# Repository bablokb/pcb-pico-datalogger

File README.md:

Pico Datalogger with Integrated Power-Management
================================================

This repository is no longer maintained, since it was split up
into independent repositories:

Software
--------

  - <https://github.com/bablokb//cp-datalogger>:
    CircuitPython Framework for Power-Optimized, Low-Frequency Datalogging

PCB
---

  - <https://github.com/bablokb//pcb-datalogger-v4e>:
    Stripped down Pico board for data-logging.
    No power-management and no XTSD storage, but Ethernet ready.
  - <https://github.com/bablokb//pcb-datalogger-v3>:
    Fully equipped, all-in-one Pico board for data-logging with power-management and XTSD storage.
  - <https://github.com/bablokb//pcb-datalogger-v2>:
    Pico board for data-logging with power-management and XTSD storage. Needs the
    sensor PCB.
  - <https://github.com/bablokb//pcb-datalogger-sensor-pcb>:
    Sensor PCB for the Pico Datalogger-v2.
  - <https://github.com/bablokb//pcb-datalogger-display-adapter-v2>:
    Display-Adapter PCB with socket-connector (for datalogger-v3/v4e).
  - <https://github.com/bablokb//pcb-datalogger-display-adapter>:
    Display-Adapter PCB with SUR-connector (for datalogger-v2/v3).
  - <https://github.com/bablokb//pcb-datalogger-lora-adapter>:
    LoRa-Adapter PCB (adds SUR-connector to Adafruit-Breakout, for datalogger-v2).
  - <https://github.com/bablokb//pcb-datalogger-lora-pcb>:
    A PCB with a LoRa tranceiver and a SUR connector (for datalogger-v2).
  - <https://github.com/bablokb//pcb-datalogger-v1>:
    First generation Pico board for data-logging with power-management and SD-card storage.
  - <https://github.com/bablokb//pcb-surs-cable-tester>:
    A small PCB to test the type of a 8-pin SUR cable.

3D-Files
--------

  - <https://github.com/bablokb//3D-datalogger-v3-case>:
    3D Design Files for a Case for the Pico-Datalogger-v3
  - <https://github.com/bablokb//3D-datalogger-v2-case>:
    3D Design Files for a Case for the Pico-Datalogger-v2
  - <https://github.com/bablokb//3D-datalogger-stevenson>:
    3D-design-files (supports, OpenSCAD) for a Stevenson Screen Enclosure
  - <https://github.com/bablokb//3D-datalogger-v1-case>:
    3D Design Files for a Case for the Pico-Datalogger-v1

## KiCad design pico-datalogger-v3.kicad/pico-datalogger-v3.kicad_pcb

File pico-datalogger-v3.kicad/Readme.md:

KiCAD-Designfiles for Version 3 PCB
===================================

Here are the KiCAD (v7) design-files for the Datalogger-V3-PCB.

Schematic
---------

Layout
------

3D-Views
--------

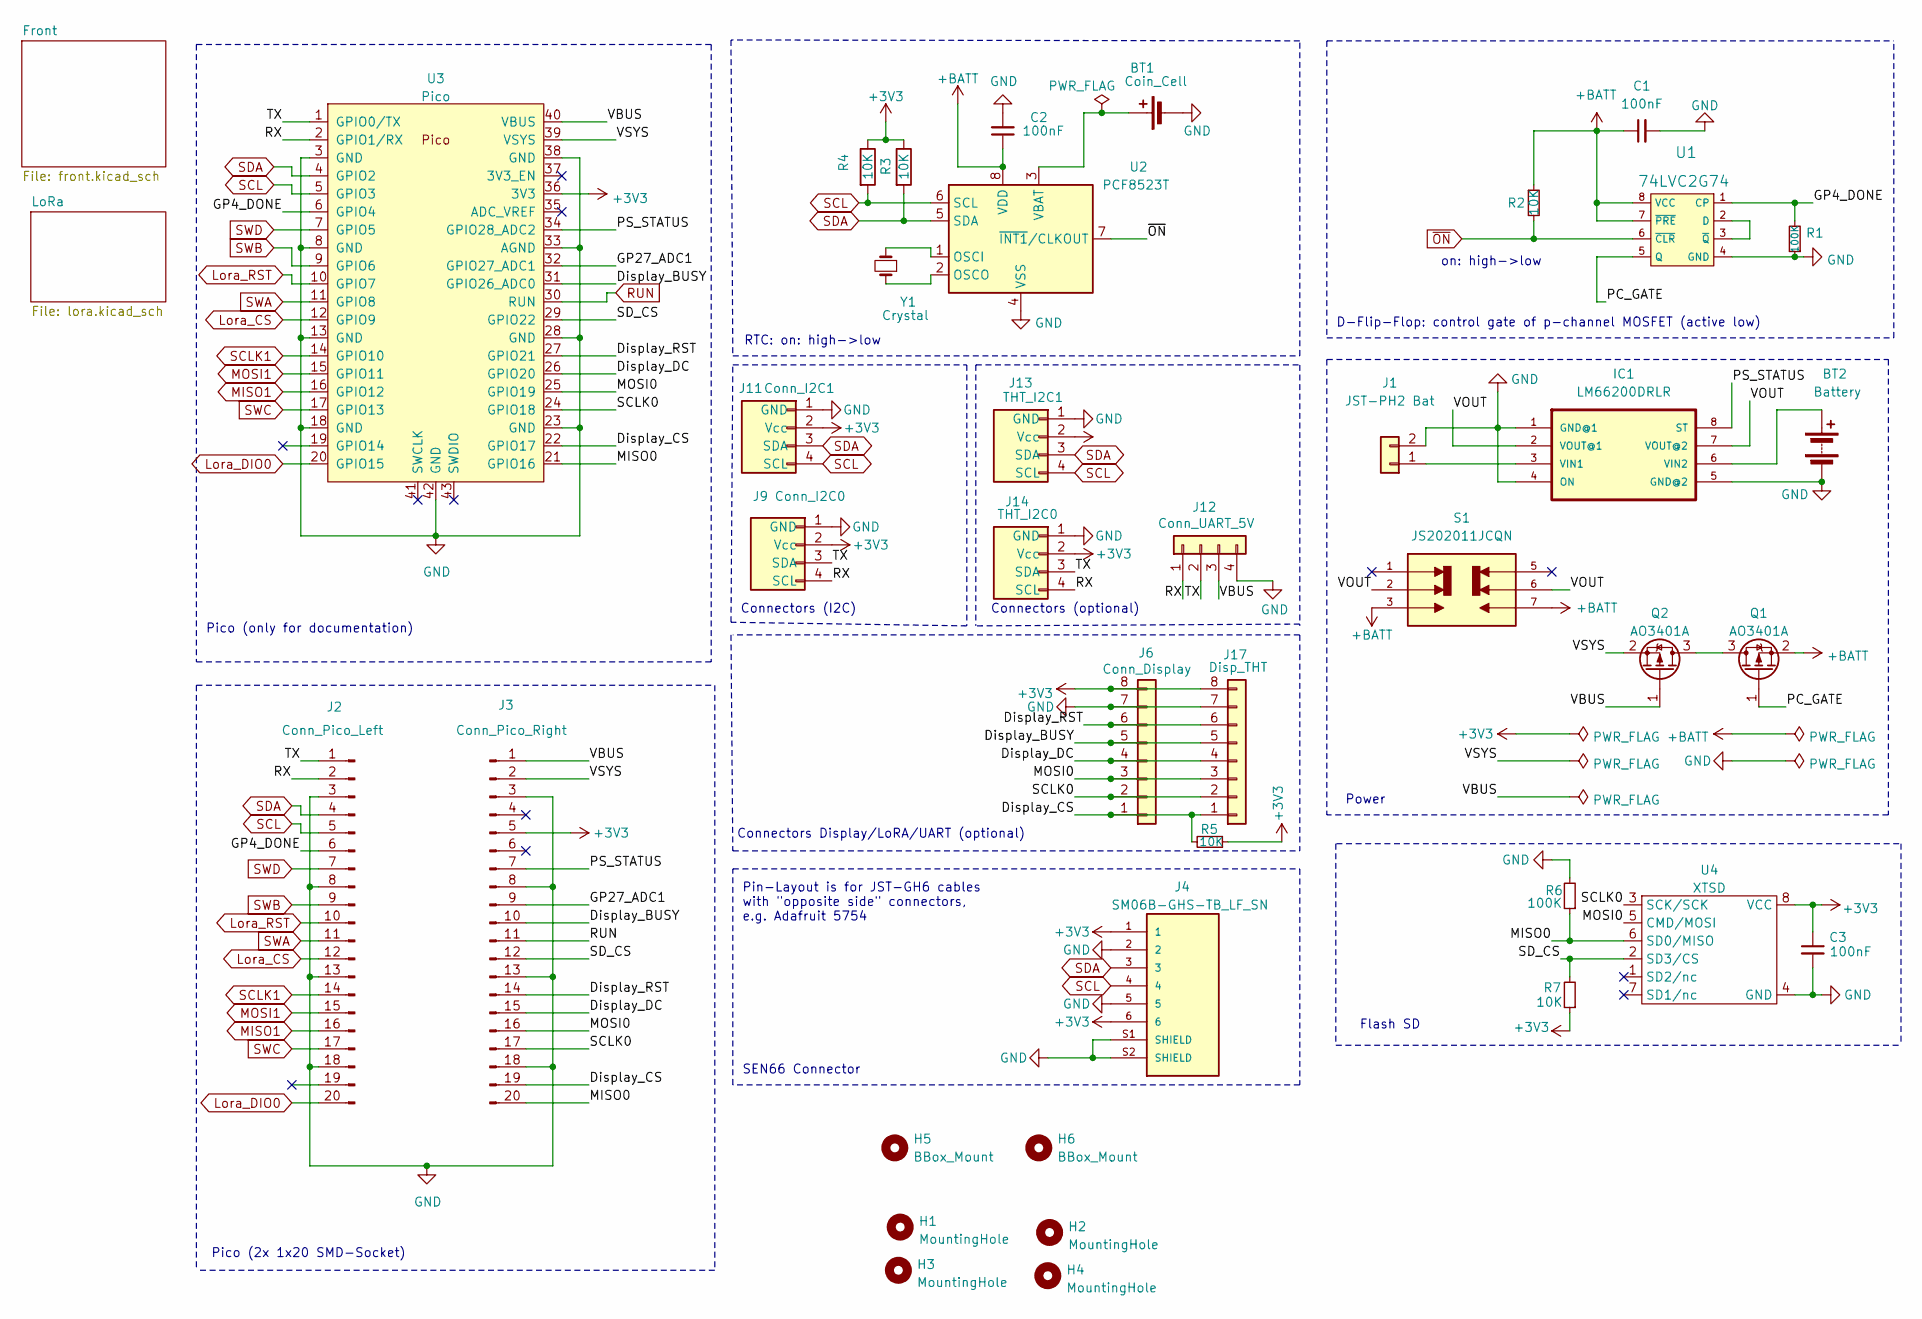
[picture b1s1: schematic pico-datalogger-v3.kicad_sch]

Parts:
BT1: Coin_Cell; CR2032_Holder; LCSC C964777
BT2: Battery; BatteryHolder_Keystone_2462_2xAA; LCSC C3029547
C1, C2, C3: 100nF; C_0402_1005Metric; LCSC C1525
H1, H2, H3, H4: MountingHole; MountingHole_2.5mm
H5, H6: BBox_Mount; MountingHole_3.5_slotted
IC1: LM66200DRLR; LCSC C3235556
J1: JST-PH2 Bat; JST_PH_S2B-PH-SM4-TB_1x02-1MP_P2.00mm_Horizontal; LCSC C295747
J2: Conn_Pico_Left; PinSocket_1x20_P2.54mm_Vertical; LCSC C429947
J3: Conn_Pico_Right; PinSocket_1x20_P2.54mm_Vertical; LCSC C429947
J4: SM06B-GHS-TB_LF_SN; JST_SM06B-GHS-TB_LF_SN; LCSC C133065
J6: Conn_Display; JST_SUR_BM08B-SURS-TF_1x08-1MP_P0.80mm_Vertical; LCSC C5143489
J9: Conn_I2C0; JST_SH_SM04B-SRSS-TB_1x04-1MP_P1.00mm_Horizontal; LCSC C160404
J11: Conn_I2C1; JST_SH_SM04B-SRSS-TB_1x04-1MP_P1.00mm_Horizontal; LCSC C160404
J12: Conn_UART_5V; PinHeader_1x04_P2.54mm_Horizontal
J13: THT_I2C1; PinHeader_1x04_P2.54mm_Vertical
J14: THT_I2C0; PinHeader_1x04_P2.54mm_Vertical
J17: Disp_THT; PinHeader_1x08_P2.54mm_Vertical
Q1, Q2: AO3401A; SOT-23; LCSC C15127
R1, R6: 100K; R_0402_1005Metric; LCSC C25741
R2, R3, R4, R5, R7: 10K; R_0402_1005Metric; LCSC C25744
S1: JS202011JCQN; SW_JS202011JCQN; LCSC C221665
U1: 74LVC2G74; TSSOP-8_3x3mm_P0.65mm; MPN SN74HC74N; Digi-Key_PN 296-1602-5-ND
U2: PCF8523T; SOIC-8_3.9x4.9mm_P1.27mm; LCSC C2651516
U3: Pico; RPi_Pico_TH_nodbg
U4: XTSD; LCSC C7429710
Y1: Crystal; Crystal_SMD_3215-2Pin_3.2x1.5mm; LCSC C32346

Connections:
+3V3: C3.1, J3.5, J4.1, J4.6, J6.8, J9.2 (Vcc), J11.2 (Vcc), J13.2 (Vcc), J14.2 (Vcc), J17.8, R3.1, R4.1, R5.1, R7.1, U3.36 (3V3), U4.8 (VCC); also elsewhere on the board
+BATT: C1.1, C2.1, Q1.2 (S), R2.1, S1.3, S1.7, U1.7 (~PRE), U1.8 (VCC), U2.8 (VDD)
/Display_BUSY: J3.10, J6.5, J17.5, U3.31 (GPIO26_ADC0)
/Display_CS: J3.19, J6.1, J17.1, R5.2, U3.22 (GPIO17)
/Display_DC: J3.15, J6.4, J17.4, U3.26 (GPIO20)
/Display_RST: J3.14, J6.6, J17.6, U3.27 (GPIO21)
/GP4_DONE: J2.6, R1.2, U1.1 (CP), U3.6 (GPIO4)
/GP27_ADC1: J3.9, U3.32 (GPIO27_ADC1)
/MISO0: J3.20, R6.1, U3.21 (GPIO16), U4.6 (SD0/MISO)
/MOSI0: J3.16, J6.3, J17.3, U3.25 (GPIO19), U4.5 (CMD/MOSI)
/PC_GATE: Q1.1 (G), U1.5 (Q)
/PS_STATUS: IC1.8 (ST), J3.7, U3.34 (GPIO28_ADC2)
/RX: J2.2, J9.4 (SCL), J12.1, J14.4 (SCL), U3.2 (GPIO1/RX)
/SCLK0: J3.17, J6.2, J17.2, U3.24 (GPIO18), U4.3 (SCK/SCK)
/SD_CS: J3.12, R7.2, U3.29 (GPIO22), U4.2 (SD3/CS)
/TX: J2.1, J9.3 (SDA), J12.2, J14.3 (SDA), U3.1 (GPIO0/TX)
/VBUS: J3.1, J12.3, Q2.1 (G), U3.40 (VBUS)
/VOUT: IC1.2 (VOUT@1), IC1.7 (VOUT@2), S1.2, S1.6
/VSYS: J3.2, Q2.2 (S), U3.39 (VSYS)
GND: BT1.2 (-), BT2.2 (-), C1.2, C2.2, C3.2, IC1.1 (GND@1), IC1.4 (ON), IC1.5 (GND@2), J1.2, J2.3, J2.8, J2.13, J2.18, J3.3, J3.8, J3.13, J3.18, J4.2, J4.5, J4.S1 (SHIELD), J4.S2 (SHIELD), J6.7, J9.1 (GND), J11.1 (GND), J12.4, J13.1 (GND), J14.1 (GND), J17.7, R1.1, R6.2, U1.4 (GND), U2.4 (VSS), U3.3 (GND), U3.8 (GND), U3.13 (GND), U3.18 (GND), U3.23 (GND), U3.28 (GND), U3.33 (AGND), U3.38 (GND), U3.42 (GND), U4.4 (GND); also elsewhere on the board
Lora_CS: J2.12, U3.12 (GPIO9); also elsewhere on the board
Lora_DIO0: J2.20, U3.20 (GPIO15); also elsewhere on the board
Lora_RST: J2.10, U3.10 (GPIO7); also elsewhere on the board
MISO1: J2.16, U3.16 (GPIO12); also elsewhere on the board
MOSI1: J2.15, U3.15 (GPIO11); also elsewhere on the board
unnamed: BT1.1 (+), U2.3 (VBAT)
unnamed: BT2.1 (+), IC1.6 (VIN2)
unnamed: IC1.3 (VIN1), J1.1
unnamed: Q1.3 (D), Q2.3 (D)
unnamed: U1.2 (D), U1.3 (~Q)
unnamed: U2.1 (OSCI), Y1.2
unnamed: U2.2 (OSCO), Y1.1
RUN: J3.11; also elsewhere on the board
SCL: J2.5, J4.4, J11.4 (SCL), J13.4 (SCL), R4.2, U2.6 (SCL), U3.5 (GPIO3); also elsewhere on the board
SCLK1: J2.14, U3.14 (GPIO10); also elsewhere on the board
SDA: J2.4, J4.3, J11.3 (SDA), J13.3 (SDA), R3.2, U2.5 (SDA), U3.4 (GPIO2); also elsewhere on the board
SWA: J2.11, U3.11 (GPIO8); also elsewhere on the board
SWB: J2.9, U3.9 (GPIO6); also elsewhere on the board
SWC: J2.17, U3.17 (GPIO13); also elsewhere on the board
SWD: J2.7, U3.7 (GPIO5); also elsewhere on the board
~ON: R2.2, U1.6 (~CLR), U2.7 (~INT1/CLKOUT); also elsewhere on the board

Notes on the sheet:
on: high->low
D-Flip-Flop: control gate of p-channel MOSFET (active low)
Connectors Display/LoRA/UART (optional)
Pico (only for documentation)
Power
Pico (2x 1x20 SMD-Socket)
SEN66 Connector
RTC: on: high->low
Connectors (optional)
Pin-Layout is for JST-GH6 cables with "opposite side" connectors, e.g. Adafruit 5754
Connectors (I2C)
Flash SD

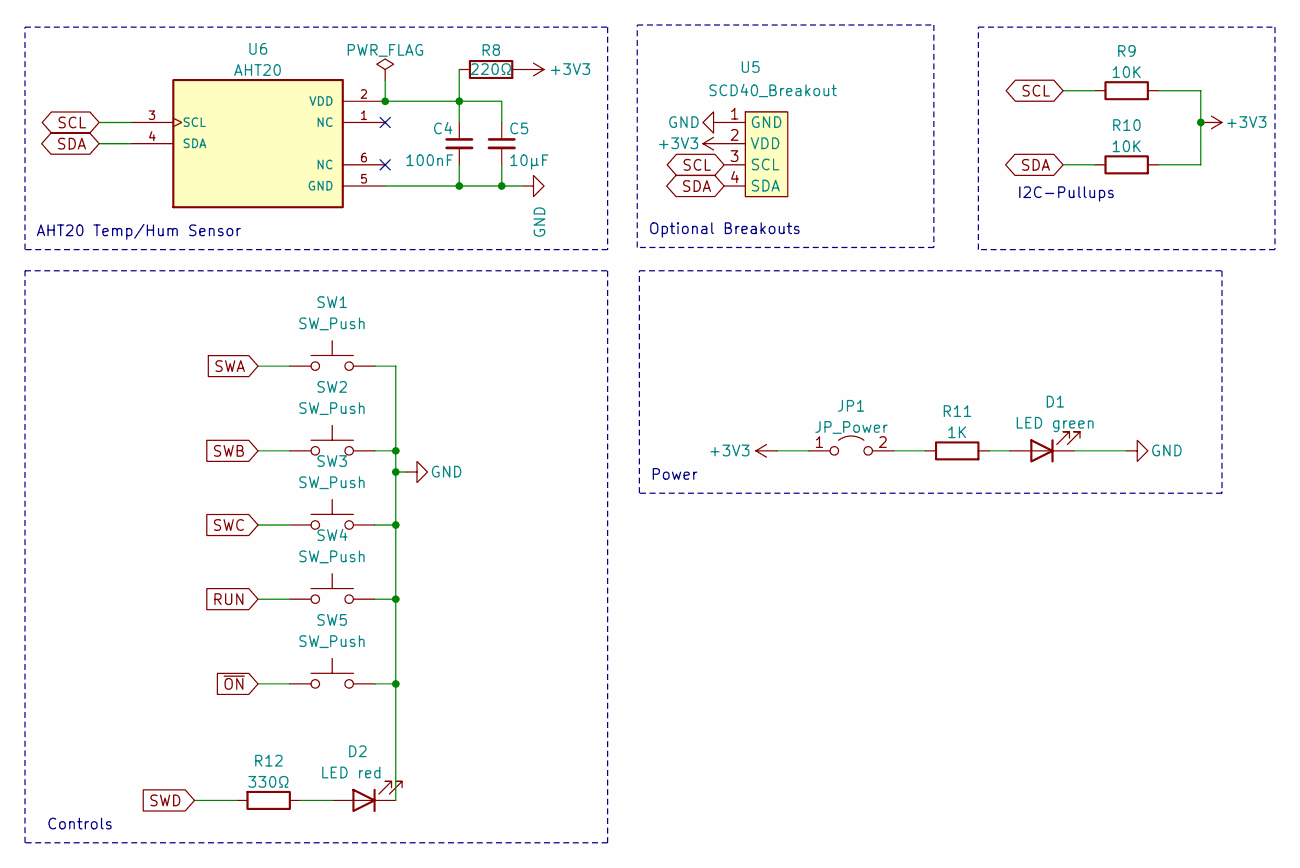
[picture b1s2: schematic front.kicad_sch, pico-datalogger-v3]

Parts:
C4: 100nF; C_0402_1005Metric; LCSC C1525
C5: 10µF; C_0603_1608Metric; LCSC C19702
D1: LED green; LED_0805_2012Metric; LCSC C2297
D2: LED red; LED_0805_2012Metric; LCSC C84256
JP1: JP_Power; SolderJumper-2_P1.3mm_Open_Pad1.0x1.5mm
R8: 220Ω; R_0402_1005Metric; LCSC C25091
R9, R10: 10K; R_0402_1005Metric; LCSC C25744
R11: 1K; R_0402_1005Metric; LCSC C11702
R12: 330Ω; R_0402_1005Metric; LCSC C25104
SW1, SW2, SW3, SW4, SW5: SW_Push; SW_SPST_B3S-1000; LCSC C221869
U5: SCD40_Breakout
U6: AHT20; LCSC C3012622

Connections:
+3V3: JP1.1 (A), R8.2, R9.2, R10.2, U5.2 (VDD); also elsewhere on the board
GND: C4.2, C5.2, D1.1 (K), D2.1 (K), SW1.2, SW2.2, SW3.2, SW4.2, SW5.2, U5.1 (GND), U6.5 (GND); also elsewhere on the board
unnamed: D1.2 (A), R11.2
unnamed: D2.2 (A), R12.1
unnamed: JP1.2 (B), R11.1
unnamed: C4.1, C5.1, R8.1, U6.2 (VDD)
RUN: SW4.1; also elsewhere on the board
SCL: R9.1, U5.3 (SCL), U6.3 (SCL); also elsewhere on the board
SDA: R10.1, U5.4 (SDA), U6.4 (SDA); also elsewhere on the board
SWA: SW1.1; also elsewhere on the board
SWB: SW2.1; also elsewhere on the board
SWC: SW3.1; also elsewhere on the board
SWD: R12.2; also elsewhere on the board
~ON: SW5.1; also elsewhere on the board

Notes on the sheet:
Optional Breakouts
AHT20 Temp/Hum Sensor
Power
I2C-Pullups
Controls

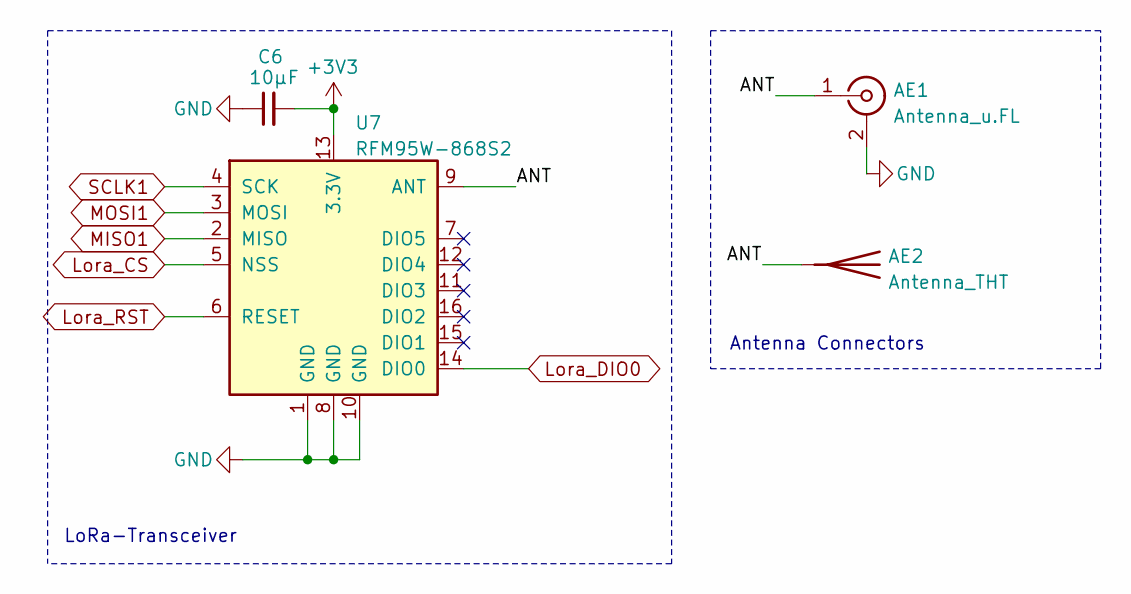
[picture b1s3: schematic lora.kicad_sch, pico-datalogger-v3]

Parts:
AE1: Antenna_u.FL; U.FL_Hirose_U.FL-R-SMT-1_Vertical; LCSC C88374
AE2: Antenna_THT
C6: 10µF; C_0603_1608Metric; LCSC C19702
U7: RFM95W-868S2; HOPERF_RFM9XW_SMD; LCSC C2844472

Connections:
+3V3: C6.2, U7.13 (3.3V); also elsewhere on the board
/LoRa/ANT: AE1.1 (In), AE2.1 (A), U7.9 (ANT)
GND: AE1.2 (Ext), C6.1, U7.1 (GND), U7.8 (GND), U7.10 (GND); also elsewhere on the board
Lora_CS: U7.5 (NSS); also elsewhere on the board
Lora_DIO0: U7.14 (DIO0); also elsewhere on the board
Lora_RST: U7.6 (RESET); also elsewhere on the board
MISO1: U7.2 (MISO); also elsewhere on the board
MOSI1: U7.3 (MOSI); also elsewhere on the board
SCLK1: U7.4 (SCK); also elsewhere on the board

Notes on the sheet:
Antenna Connectors
LoRa-Transceiver

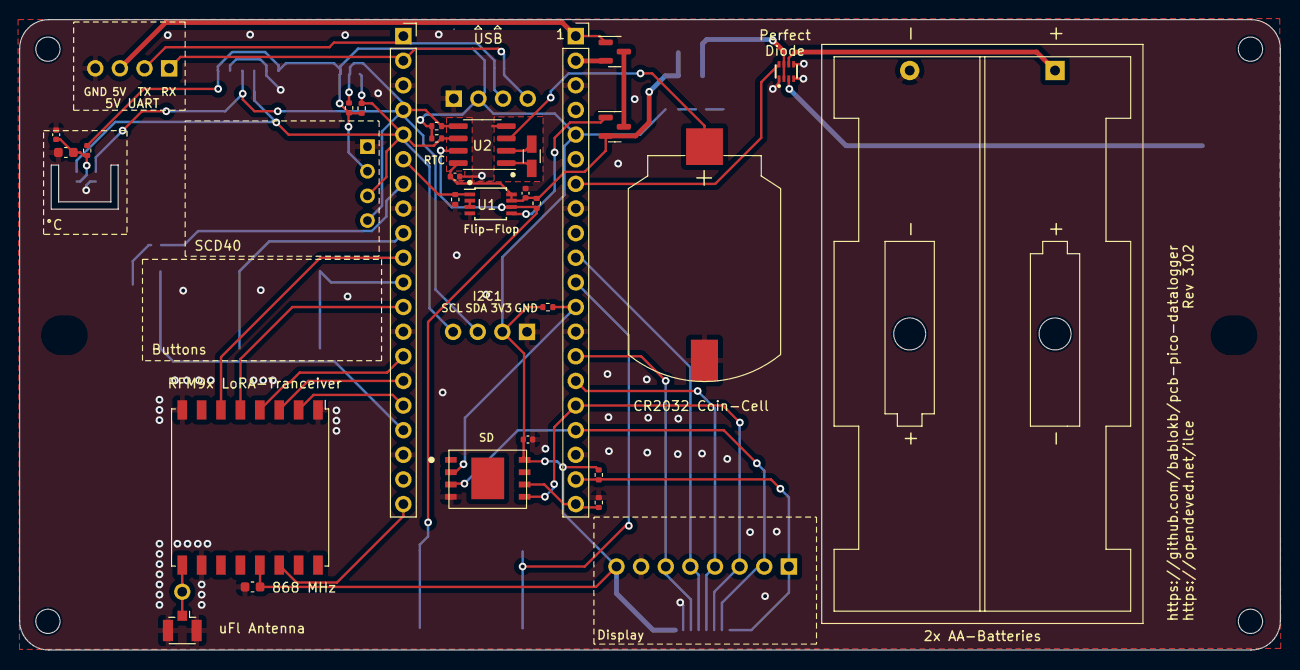
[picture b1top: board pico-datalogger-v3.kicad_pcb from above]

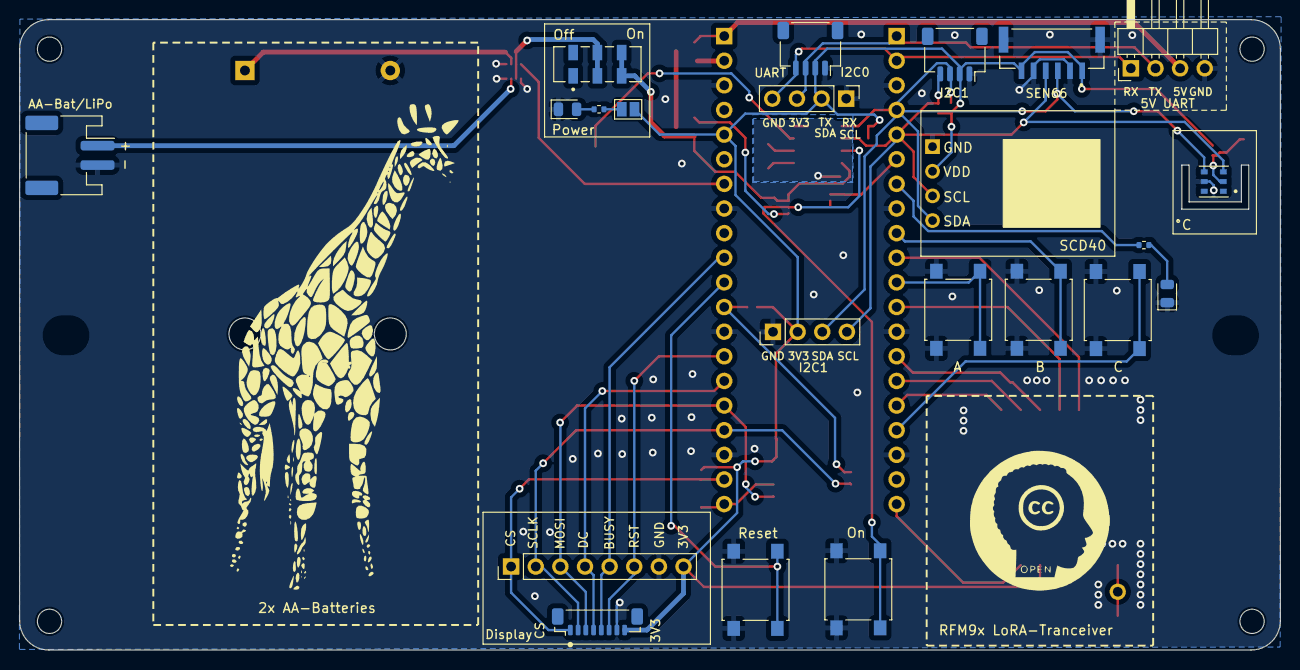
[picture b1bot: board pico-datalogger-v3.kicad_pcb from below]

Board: 2 copper layers, 130.0 x 65.0 mm, 58 parts (22 on the bottom side), 45 nets.

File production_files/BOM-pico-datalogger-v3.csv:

Comment,Designator,Footprint,LCSC
1K,R11,R_0402_1005Metric,C11702
SM06B-GHS-TB_LF_SN,J4,JST_SM06B-GHS-TB_LF_SN,C133065
AO3401A,"Q1,Q2",SOT-23,C15127
100nF,"C1,C2,C3,C4",C_0402_1005Metric,C1525
Conn_I2C1,"J11,J9",JST_SH_SM04B-SRSS-TB_1x04-1MP_P1.00mm_Horizontal,C160404
10µF,"C5,C6",C_0603_1608Metric,C19702
JS202011JCQN,S1,SW_JS202011JCQN,C221665
SW_Push,"SW1,SW2,SW3,SW4,SW5",SW_SPST_B3S-1000,C221869
LED green,D1,LED_0805_2012Metric,C2297
220Ω,R8,R_0402_1005Metric,C25091
330Ω,R12,R_0402_1005Metric,C25104
100K,"R1,R6",R_0402_1005Metric,C25741
10K,"R10,R2,R3,R4,R5,R7,R9",R_0402_1005Metric,C25744
PCF8523T,U2,SOIC-8_3.9x4.9mm_P1.27mm,C2651516
74LVC2G74,U1,TSSOP-8_3x3mm_P0.65mm,C282355
RFM95W-868S2,U7,HOPERF_RFM9XW_SMD,C2844472
JST-PH2 Bat,J1,JST_PH_S2B-PH-SM4-TB_1x02-1MP_P2.00mm_Horizontal,C295747
AHT20,U6,AHT20,C3012622
Battery,BT2,BatteryHolder_Keystone_2462_2xAA,C3029547
Crystal,Y1,Crystal_SMD_3215-2Pin_3.2x1.5mm,C32346
LM66200DRLR,IC1,LM66200DRLR,C3235556
Conn_Pico_Left,"J2,J3",PinSocket_1x20_P2.54mm_Vertical,C429947
Conn_Display,J6,JST_SUR_BM08B-SURS-TF_1x08-1MP_P0.80mm_Vertical,C5143489
XTSD,U4,XTSD,C7429710
LED red,D2,LED_0805_2012Metric,C84256
Antenna_u.FL,AE1,U.FL_Hirose_U.FL-R-SMT-1_Vertical,C88374
Coin_Cell,BT1,CR2032_Holder,C964777

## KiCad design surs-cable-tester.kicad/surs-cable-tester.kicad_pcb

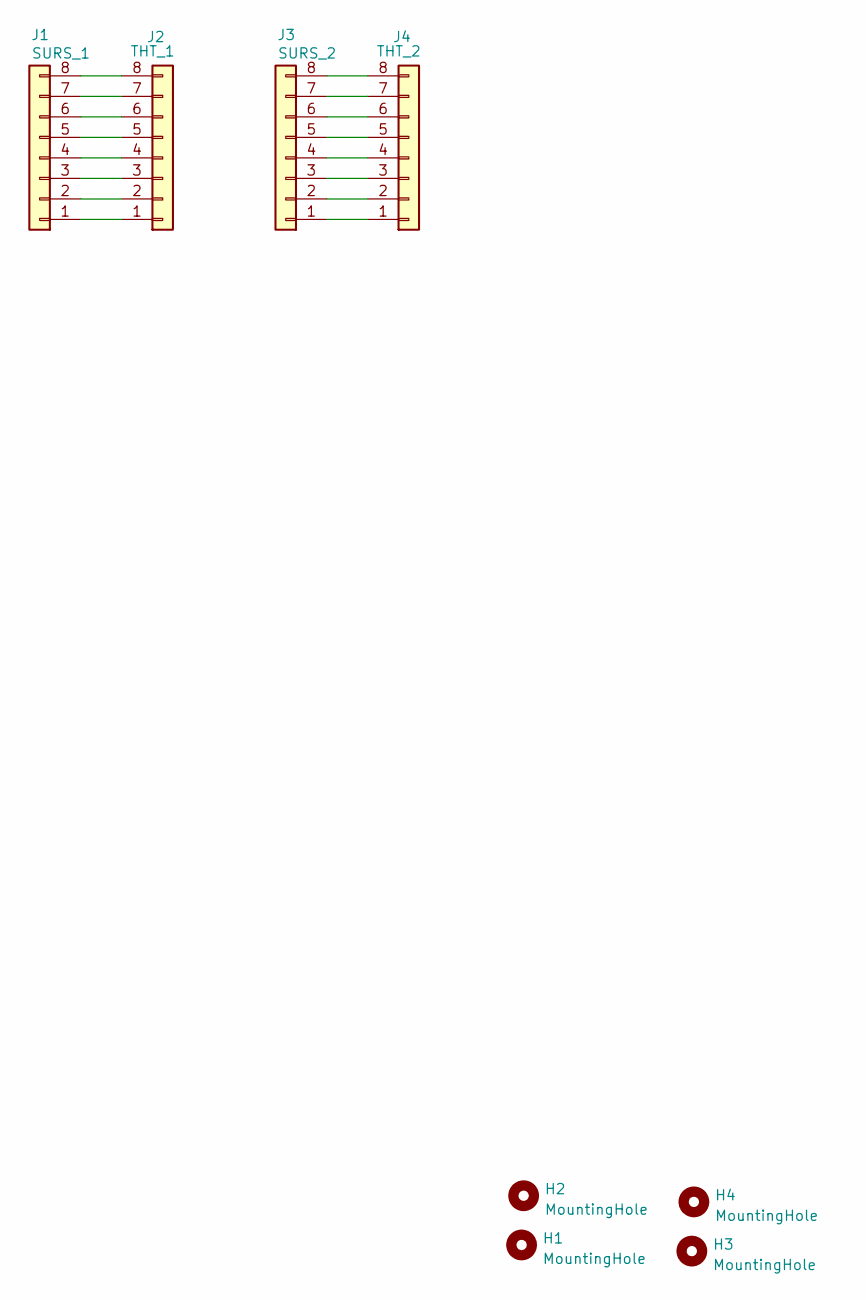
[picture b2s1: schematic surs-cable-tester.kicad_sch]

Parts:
H1, H2, H3, H4: MountingHole; MountingHole_2.5mm
J1: SURS_1; JST_SUR_BM08B-SURS-TF_1x08-1MP_P0.80mm_Vertical; LCSC C5143489
J2: THT_1; PinHeader_1x08_P2.54mm_Vertical
J3: SURS_2; JST_SUR_BM08B-SURS-TF_1x08-1MP_P0.80mm_Vertical; LCSC C5143489
J4: THT_2; PinHeader_1x08_P2.54mm_Vertical

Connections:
unnamed: J1.1, J2.1
unnamed: J1.2, J2.2
unnamed: J1.3, J2.3
unnamed: J1.4, J2.4
unnamed: J1.5, J2.5
unnamed: J1.6, J2.6
unnamed: J1.7, J2.7
unnamed: J1.8, J2.8
unnamed: J3.1, J4.1
unnamed: J3.2, J4.2
unnamed: J3.3, J4.3
unnamed: J3.4, J4.4
unnamed: J3.5, J4.5
unnamed: J3.6, J4.6
unnamed: J3.7, J4.7
unnamed: J3.8, J4.8

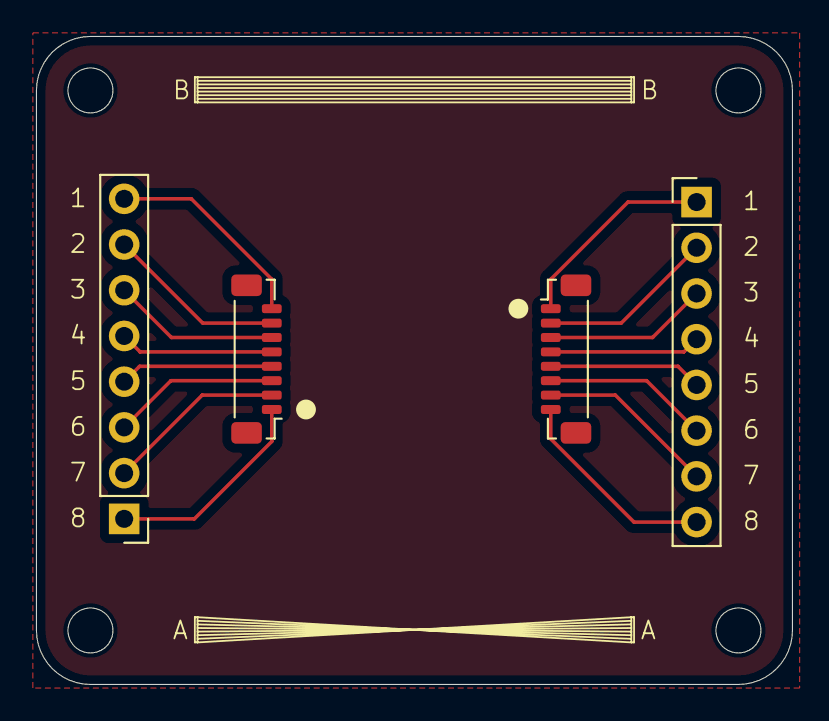
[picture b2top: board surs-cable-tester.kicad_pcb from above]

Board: 2 copper layers, 42.0 x 36.0 mm, 8 parts (0 on the bottom side), 16 nets.

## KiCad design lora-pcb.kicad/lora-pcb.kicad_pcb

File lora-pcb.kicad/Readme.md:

KiCAD-Designfiles
=================

Here are the KiCAD (v6) design-files for the LoRa-PCB.

This PCB is an integrated solution for a RFM9X-SMD-module and a
SURS-connector.

Schematic
---------

Layout
------

3D-Views
--------

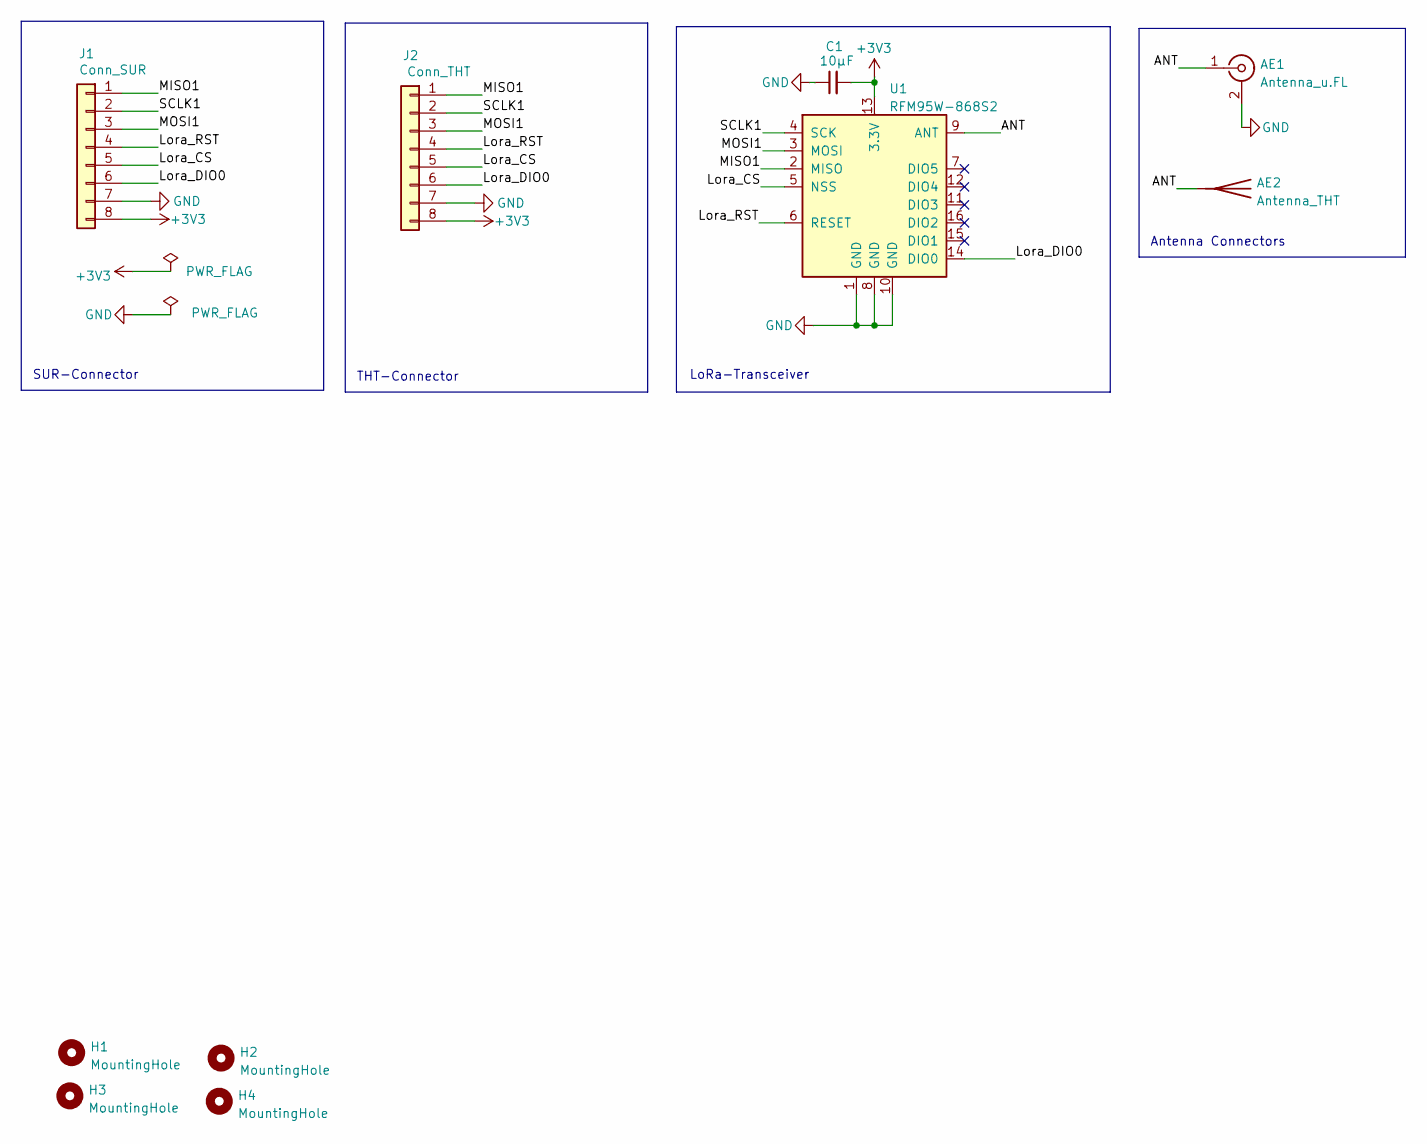
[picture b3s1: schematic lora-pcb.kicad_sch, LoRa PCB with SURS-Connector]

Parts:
AE1: Antenna_u.FL; U.FL_Hirose_U.FL-R-SMT-1_Vertical; LCSC C88374
AE2: Antenna_THT
C1: 10µF; C_0603_1608Metric; LCSC C19702
H1, H2, H3, H4: MountingHole; MountingHole_2.5mm
J1: Conn_SUR; JST_SUR_BM08B-SURS-TF_1x08-1MP_P0.80mm_Vertical; LCSC C5143489
J2: Conn_THT; PinHeader_1x08_P2.54mm_Vertical; LCSC C5143489
U1: RFM95W-868S2; HOPERF_RFM9XW_SMD; LCSC C2844474

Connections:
+3V3: C1.2, J1.8, J2.8, U1.13 (3.3V)
/ANT: AE1.1 (In), AE2.1 (A), U1.9 (ANT)
/Lora_CS: J1.5, J2.5, U1.5 (NSS)
/Lora_DIO0: J1.6, J2.6, U1.14 (DIO0)
/Lora_RST: J1.4, J2.4, U1.6 (RESET)
/MISO1: J1.1, J2.1, U1.2 (MISO)
/MOSI1: J1.3, J2.3, U1.3 (MOSI)
/SCLK1: J1.2, J2.2, U1.4 (SCK)
GND: AE1.2 (Ext), C1.1, J1.7, J2.7, U1.1 (GND), U1.8 (GND), U1.10 (GND)

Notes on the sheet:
Antenna Connectors
LoRa-Transceiver
THT-Connector
SUR-Connector

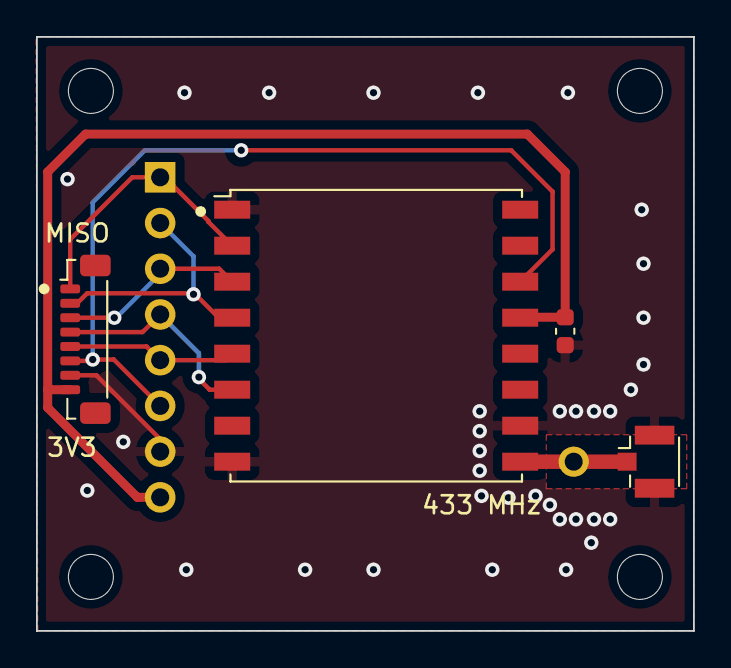
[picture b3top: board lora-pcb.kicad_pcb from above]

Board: 2 copper layers, 36.5 x 33.0 mm, 10 parts (1 on the bottom side), 9 nets.

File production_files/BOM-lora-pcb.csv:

Comment,Designator,Footprint,LCSC
10µF,C1,C_0603_1608Metric,C19702
RFM95W-868S2,U1,HOPERF_RFM9XW_SMD,C2844474
Conn_SUR,J1,JST_SUR_BM08B-SURS-TF_1x08-1MP_P0.80mm_Vertical,C5143489
Antenna_u.FL,AE1,U.FL_Hirose_U.FL-R-SMT-1_Vertical,C88374

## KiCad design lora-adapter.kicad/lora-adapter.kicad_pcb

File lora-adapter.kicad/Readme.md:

KiCAD-Designfiles
=================

Here are the KiCAD (v6) design-files for the LoRa-adapter-PCB.

Schematic
---------

Layout
------

3D-Views
--------

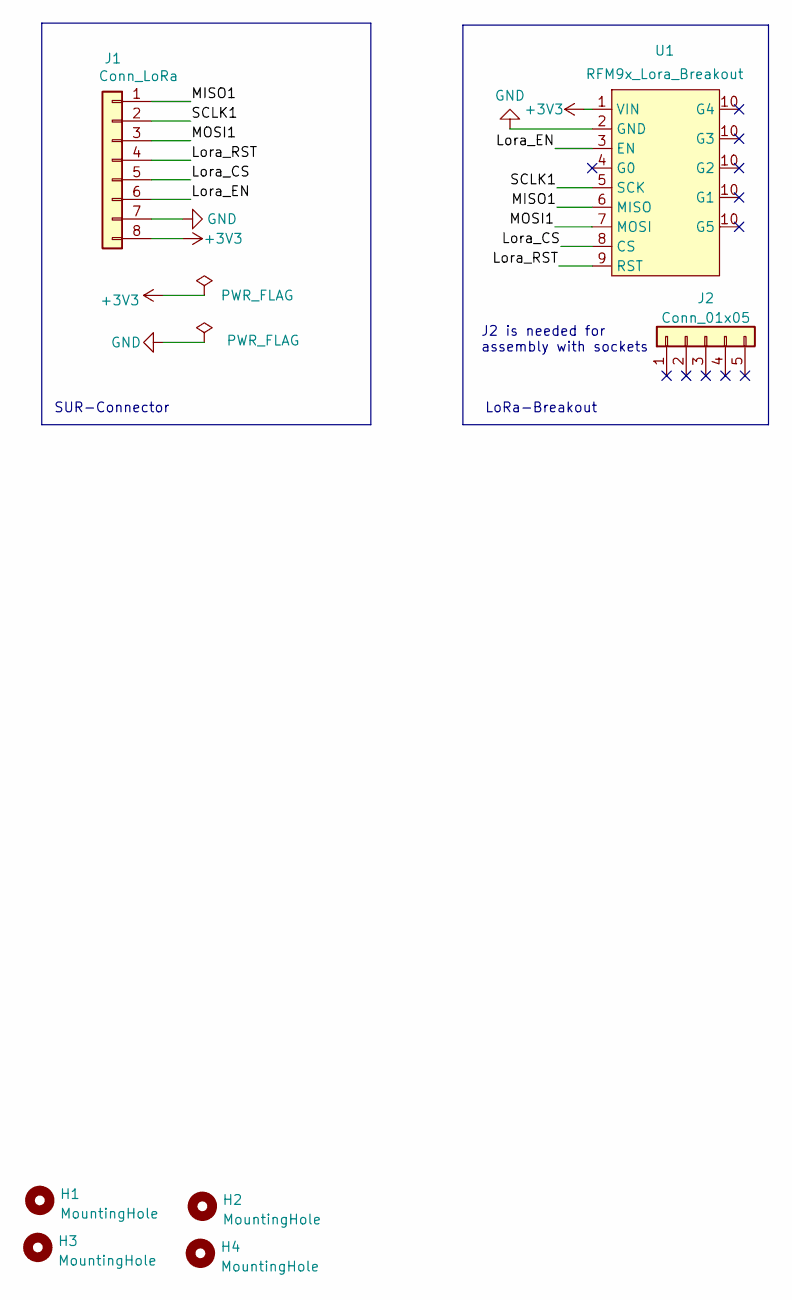
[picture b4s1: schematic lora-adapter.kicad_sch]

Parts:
H1, H2, H3, H4: MountingHole; MountingHole_2.5mm
J1: Conn_LoRa; JST_SUR_BM08B-SURS-TF_1x08-1MP_P0.80mm_Vertical; LCSC C5143489
J2: Conn_01x05; PinSocket_1x05_P2.54mm_Vertical; LCSC C2897368
U1: RFM9x_Lora_Breakout; PinSocket_1x09_P2.54mm_Vertical; LCSC C2897372

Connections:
+3V3: J1.8, U1.1 (VIN)
/Lora_CS: J1.5, U1.8 (CS)
/Lora_EN: J1.6, U1.3 (EN)
/Lora_RST: J1.4, U1.9 (RST)
/MISO1: J1.1, U1.6 (MISO)
/MOSI1: J1.3, U1.7 (MOSI)
/SCLK1: J1.2, U1.5 (SCK)
GND: J1.7, U1.2 (GND)

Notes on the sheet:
J2 is needed for assembly with sockets
LoRa-Breakout
SUR-Connector

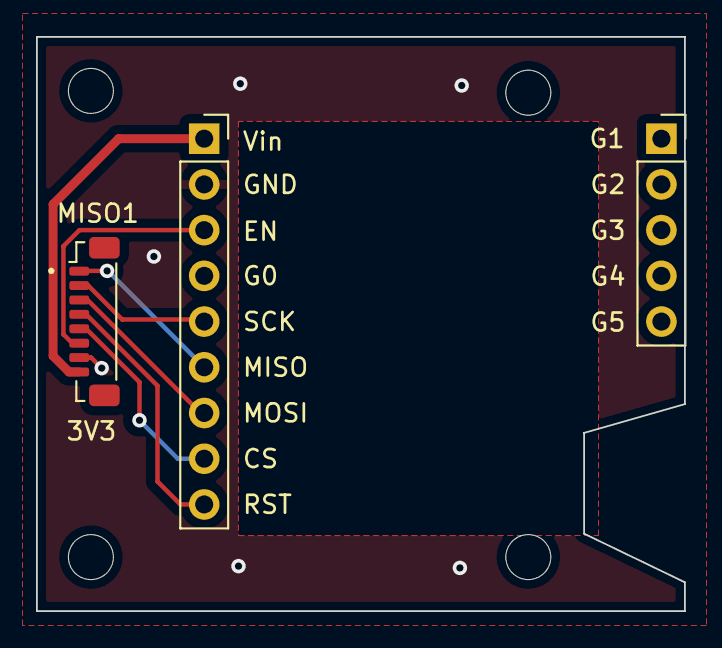
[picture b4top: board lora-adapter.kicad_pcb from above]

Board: 2 copper layers, 36.0 x 31.9 mm, 7 parts (0 on the bottom side), 8 nets.

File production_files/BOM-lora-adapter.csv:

Comment,Designator,Footprint,LCSC
Conn_01x05,J2,PinSocket_1x05_P2.54mm_Vertical,C2897368
RFM9x_Lora_Breakout,U1,PinSocket_1x09_P2.54mm_Vertical,C2897372
Conn_LoRa,J1,JST_SUR_BM08B-SURS-TF_1x08-1MP_P0.80mm_Vertical,C5143489

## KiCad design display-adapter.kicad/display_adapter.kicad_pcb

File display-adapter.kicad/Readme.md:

KiCAD-Designfiles
=================

Here are the KiCAD (v6) design-files for the display-adapter-PCB.

Schematic
---------

Layout
------

3D-Views
--------

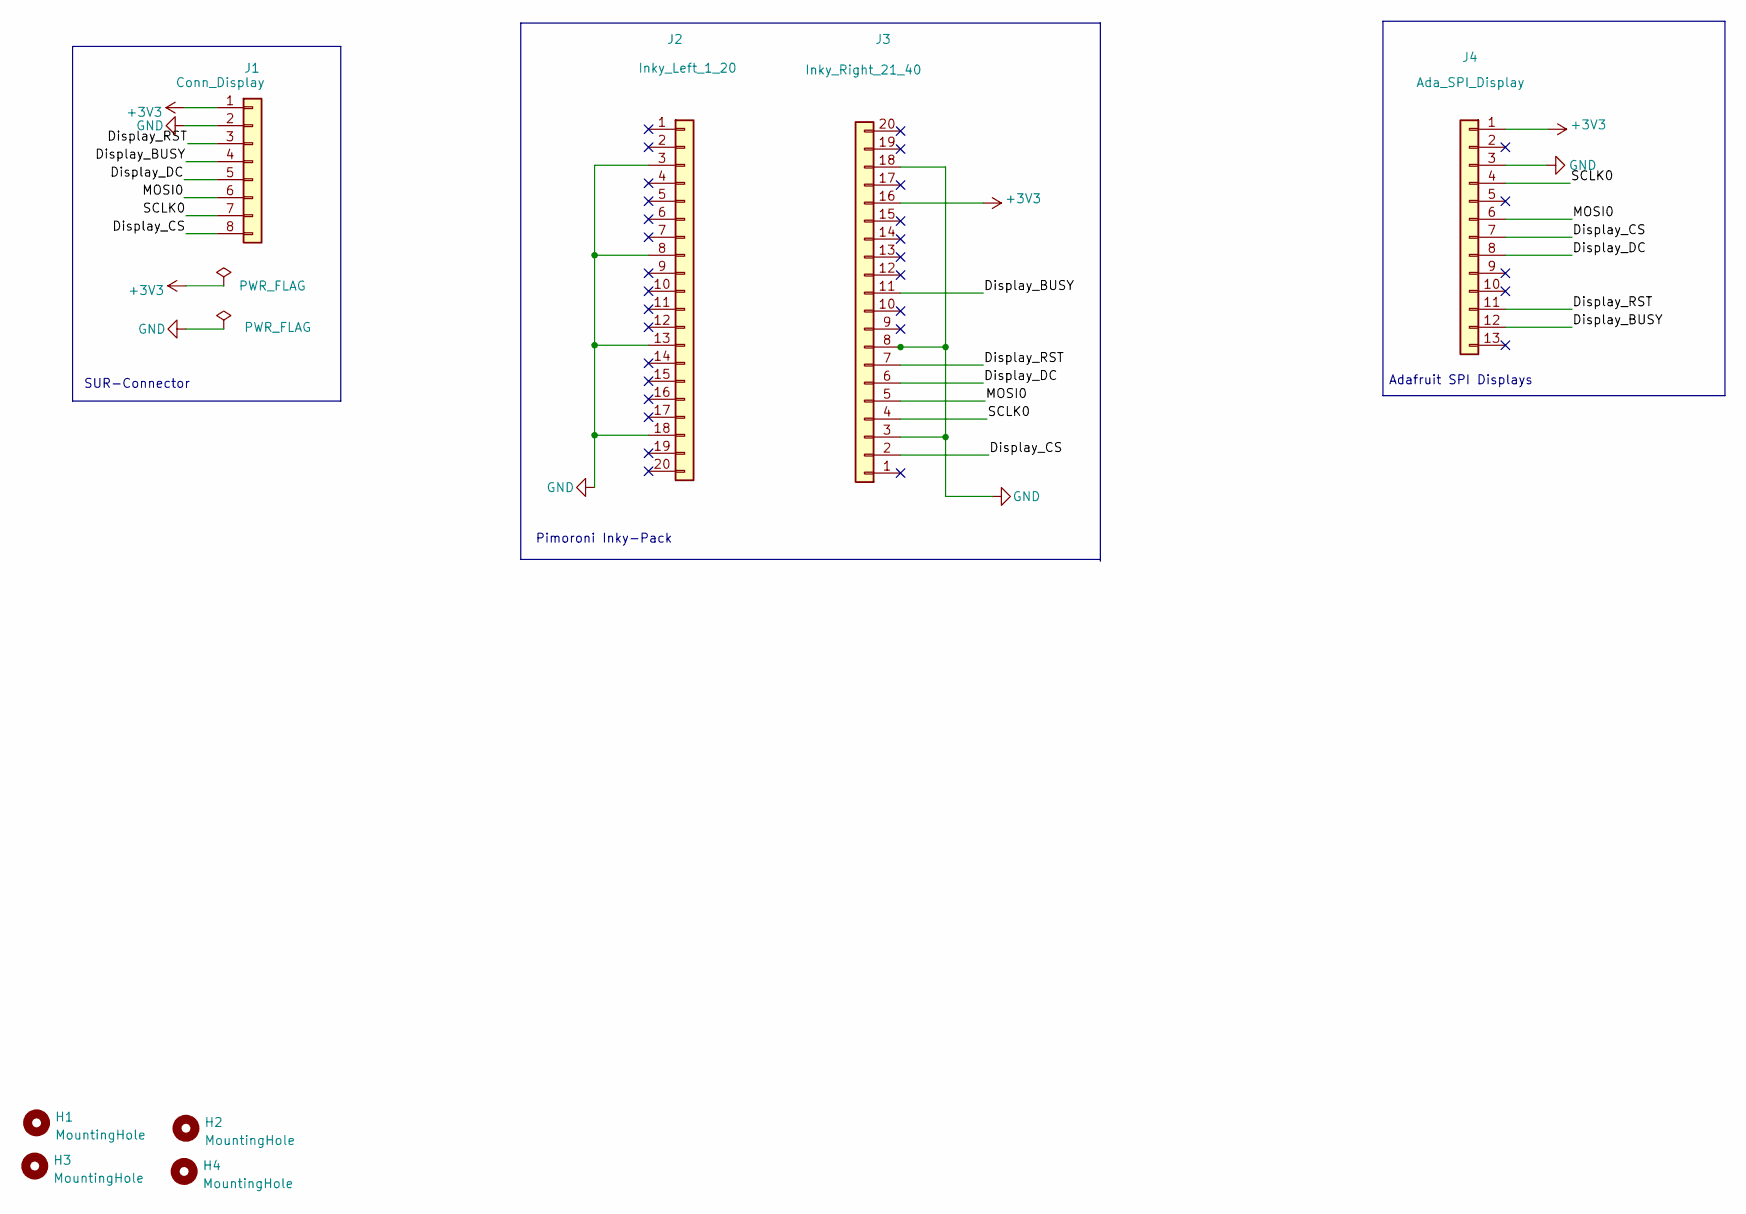
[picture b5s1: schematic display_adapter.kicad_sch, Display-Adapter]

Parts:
H1, H2, H3, H4: MountingHole; MountingHole_2.5mm
J1: Conn_Display; JST_SUR_BM08B-SURS-TF_1x08-1MP_P0.80mm_Vertical; LCSC C5143489
J2: Inky_Left_1_20; PinHeader_1x20_P2.54mm_Vertical; LCSC C725952
J3: Inky_Right_21_40; PinHeader_1x20_P2.54mm_Vertical; LCSC C725952
J4: Ada_SPI_Display; PinSocket_1x13_P2.54mm_Vertical

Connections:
+3V3: J1.1, J3.16, J4.1
/Display_BUSY: J1.4, J3.11, J4.12
/Display_CS: J1.8, J3.2, J4.7
/Display_DC: J1.5, J3.6, J4.8
/Display_RST: J1.3, J3.7, J4.11
/MOSI0: J1.6, J3.5, J4.6
/SCLK0: J1.7, J3.4, J4.4
GND: J1.2, J2.3, J2.8, J2.13, J2.18, J3.3, J3.8, J3.18, J4.3

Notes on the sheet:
Pimoroni Inky-Pack
Adafruit SPI Displays
SUR-Connector

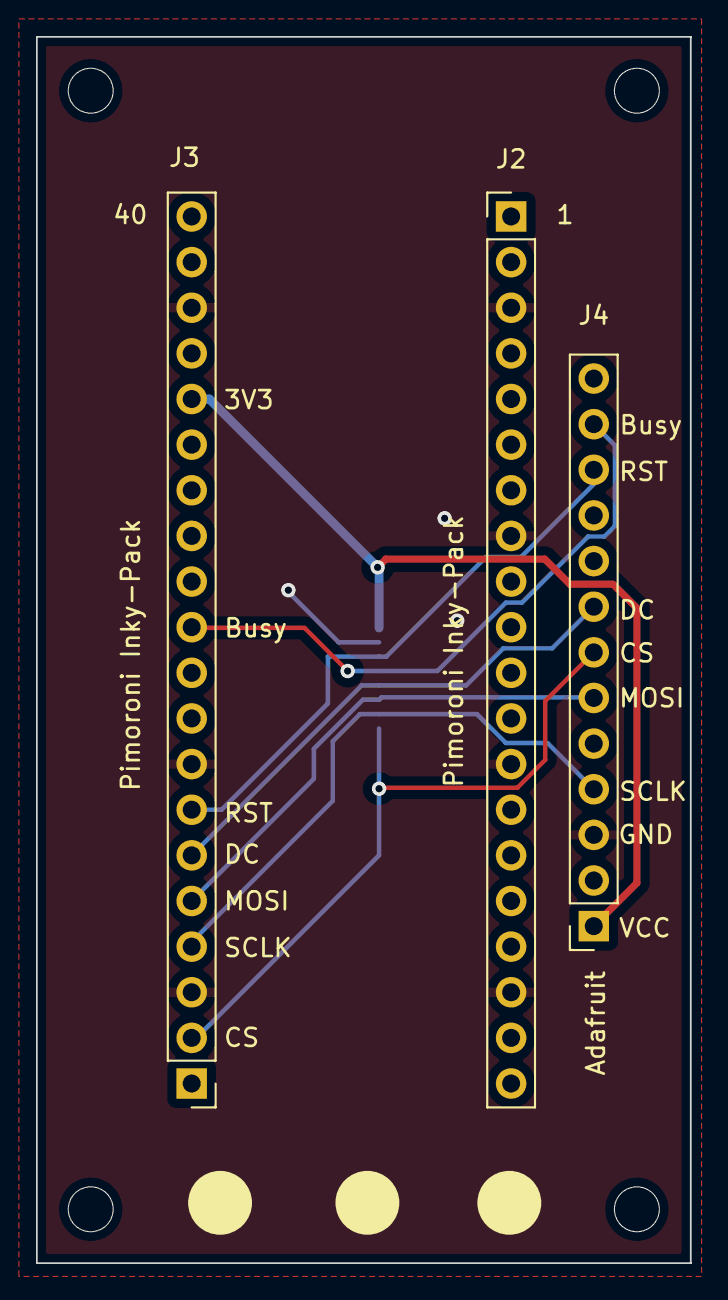
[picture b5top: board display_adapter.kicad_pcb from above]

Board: 2 copper layers, 36.4 x 68.3 mm, 8 parts (1 on the bottom side), 8 nets.
